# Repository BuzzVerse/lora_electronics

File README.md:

pliki do płytki beaglebone'a i esp32c3

Beaglebone + lora + bme280 najnowsza wersja:
https://github.com/BuzzVerse/lora_hardware/tree/main/beaglebone_gateway/v1

esp32c3 + lora + bme280 najnowsza wersja:
https://github.com/BuzzVerse/lora_hardware/tree/main/esp32_node/v1

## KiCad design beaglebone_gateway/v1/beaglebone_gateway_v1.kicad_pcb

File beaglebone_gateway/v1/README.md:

# LoRa gateway v1

This repository contains schematics and PCB for LoRa gateway HAT.

Screenshots can be found in `pdf` directory

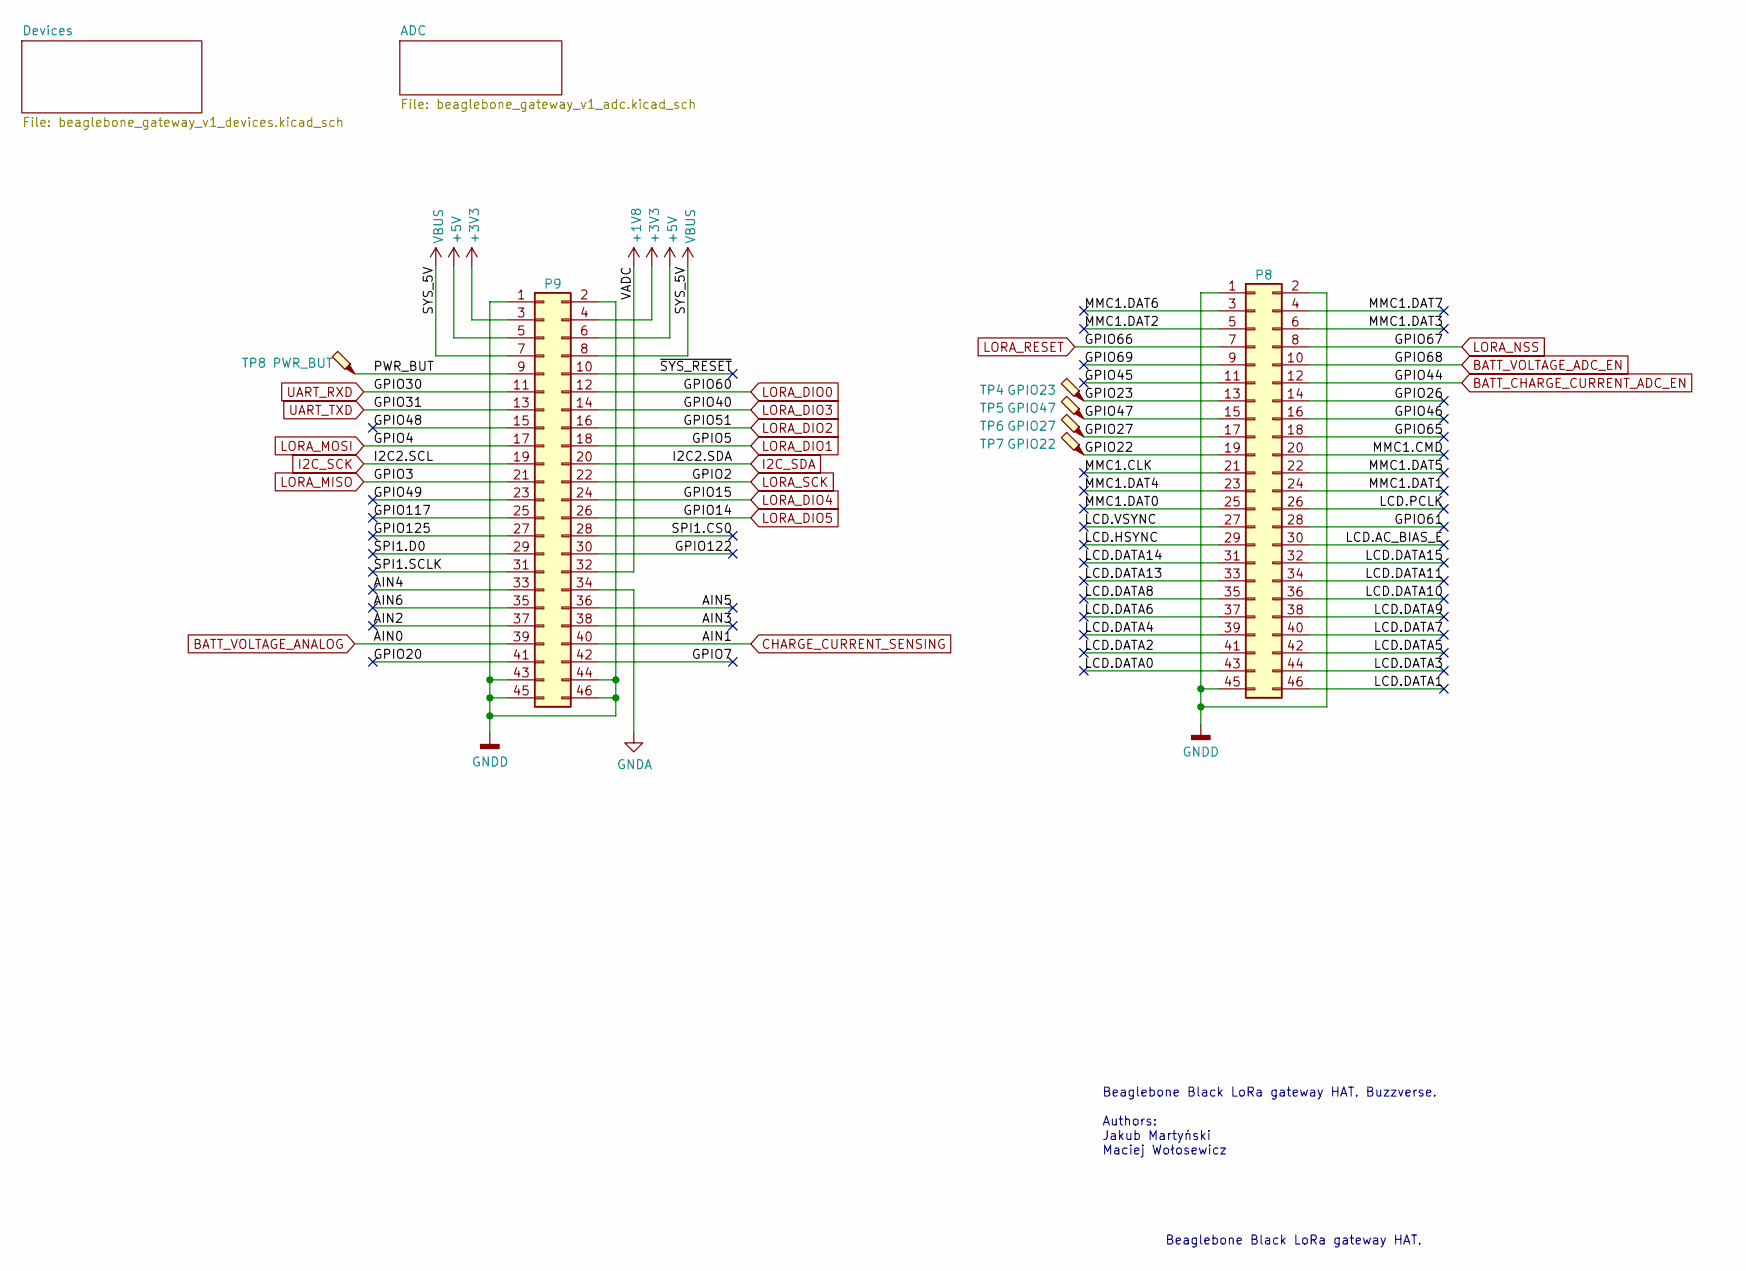
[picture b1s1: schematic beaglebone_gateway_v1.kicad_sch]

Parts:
P8, P9: BeagleBone_Black_Header; PinHeader_2x23_P2.54mm_Vertical
TP4: GPIO23; TestPoint_Pad_D1.5mm
TP5: GPIO47; TestPoint_Pad_D1.5mm
TP6: GPIO27; TestPoint_Pad_D1.5mm
TP7: GPIO22; TestPoint_Pad_D1.5mm
TP8: PWR_BUT; TestPoint_Pad_D1.5mm

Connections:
+1V8: P9.32
+3V3: P9.3, P9.4; also elsewhere on the board
+5V: P9.5, P9.6; also elsewhere on the board
/AIN2: P9.37
/AIN3: P9.38
/AIN4: P9.33
/AIN5: P9.36
/AIN6: P9.35
/GPIO7: P9.42
/GPIO20: P9.41
/GPIO22: P8.19, TP7.1
/GPIO23: P8.13, TP4.1
/GPIO26: P8.14
/GPIO27: P8.17, TP6.1
/GPIO45: P8.11
/GPIO46: P8.16
/GPIO47: P8.15, TP5.1
/GPIO48: P9.15
/GPIO49: P9.23
/GPIO61: P8.28
/GPIO65: P8.18
/GPIO69: P8.9
/GPIO117: P9.25
/GPIO122: P9.30
/GPIO125: P9.27
/LCD.AC_BIAS_E: P8.30
/LCD.DATA0: P8.43
/LCD.DATA1: P8.46
/LCD.DATA2: P8.41
/LCD.DATA3: P8.44
/LCD.DATA4: P8.39
/LCD.DATA5: P8.42
/LCD.DATA6: P8.37
/LCD.DATA7: P8.40
/LCD.DATA8: P8.35
/LCD.DATA9: P8.38
/LCD.DATA10: P8.36
/LCD.DATA11: P8.34
/LCD.DATA13: P8.33
/LCD.DATA14: P8.31
/LCD.DATA15: P8.32
/LCD.HSYNC: P8.29
/LCD.PCLK: P8.26
/LCD.VSYNC: P8.27
/MMC1.CLK: P8.21
/MMC1.CMD: P8.20
/MMC1.DAT0: P8.25
/MMC1.DAT1: P8.24
/MMC1.DAT2: P8.5
/MMC1.DAT3: P8.6
/MMC1.DAT4: P8.23
/MMC1.DAT5: P8.22
/MMC1.DAT6: P8.3
/MMC1.DAT7: P8.4
/PWR_BUT: P9.9, TP8.1
/SPI1.CS0: P9.28
/SPI1.D0: P9.29
/SPI1.SCLK: P9.31
/~SYS_RESET: P9.10
BATT_CHARGE_CURRENT_ADC_EN: P8.12; also elsewhere on the board
BATT_VOLTAGE_ADC_EN: P8.10; also elsewhere on the board
BATT_VOLTAGE_ANALOG: P9.39; also elsewhere on the board
CHARGE_CURRENT_SENSING: P9.40; also elsewhere on the board
GNDA: P9.34; also elsewhere on the board
GNDD: P8.1, P8.2, P8.45, P9.1, P9.2, P9.43, P9.44, P9.45, P9.46; also elsewhere on the board
I2C_SCK: P9.19; also elsewhere on the board
I2C_SDA: P9.20; also elsewhere on the board
LORA_DIO0: P9.12; also elsewhere on the board
LORA_DIO1: P9.18; also elsewhere on the board
LORA_DIO2: P9.16; also elsewhere on the board
LORA_DIO3: P9.14; also elsewhere on the board
LORA_DIO4: P9.24; also elsewhere on the board
LORA_DIO5: P9.26; also elsewhere on the board
LORA_MISO: P9.21; also elsewhere on the board
LORA_MOSI: P9.17; also elsewhere on the board
LORA_NSS: P8.8; also elsewhere on the board
LORA_RESET: P8.7; also elsewhere on the board
LORA_SCK: P9.22; also elsewhere on the board
UART_RXD: P9.11; also elsewhere on the board
UART_TXD: P9.13; also elsewhere on the board
VBUS: P9.7, P9.8

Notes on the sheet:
Beaglebone Black LoRa gateway HAT.
Beaglebone Black LoRa gateway HAT. Buzzverse. Authors: Jakub Martyński Maciej Wołosewicz

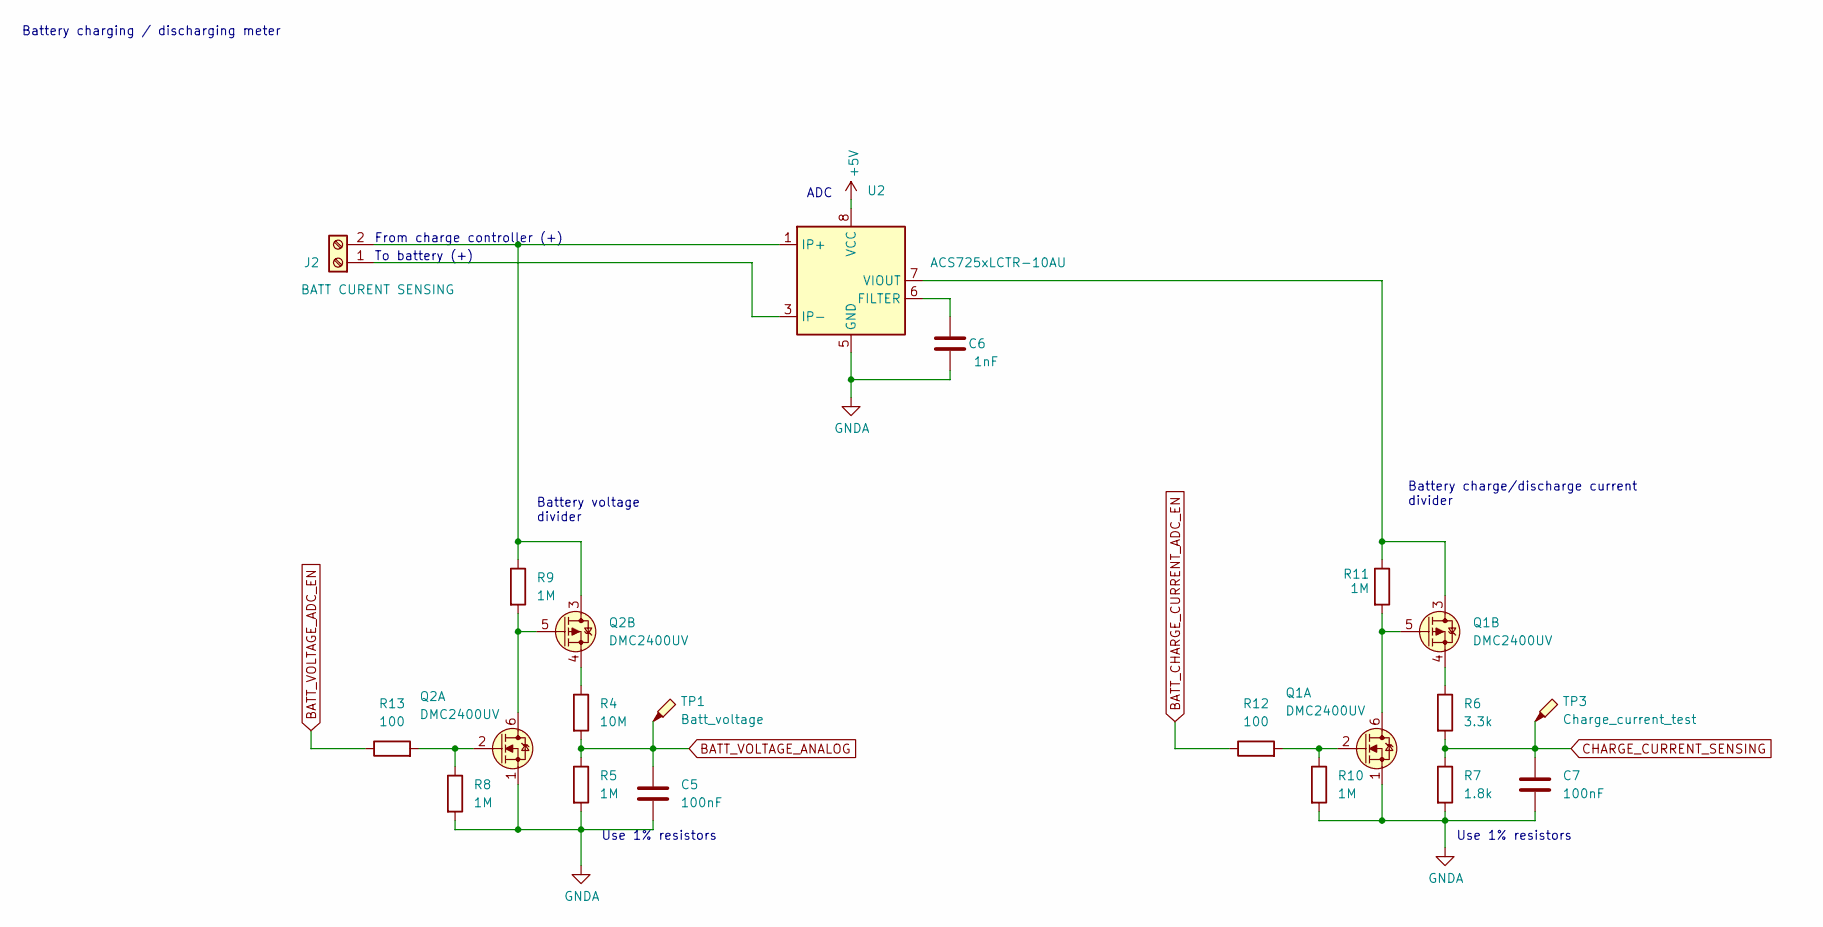
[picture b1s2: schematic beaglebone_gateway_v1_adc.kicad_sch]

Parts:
C5, C7: 100nF; C_0603_1608Metric
C6: 1nF; C_0603_1608Metric
J2: BATT CURENT SENSING; TerminalBlock_Phoenix_PT-1,5-2-3.5-H_1x02_P3.50mm_Horizontal
Q1, Q2: DMC2400UV; SOT-563
R4: 10M; R_0603_1608Metric
R5, R8, R9, R10, R11: 1M; R_0603_1608Metric
R6: 3.3k; R_0603_1608Metric
R7: 1.8k; R_0603_1608Metric
R12, R13: 100; R_0603_1608Metric
TP1: Batt_voltage; TestPoint_Pad_D1.5mm
TP3: Charge_current_test; TestPoint_Pad_D1.5mm
U2: ACS725xLCTR-10AU; SOIC-8_3.9x4.9mm_P1.27mm

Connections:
+5V: U2.8 (VCC); also elsewhere on the board
BATT_CHARGE_CURRENT_ADC_EN: R12.1; also elsewhere on the board
BATT_VOLTAGE_ADC_EN: R13.1; also elsewhere on the board
BATT_VOLTAGE_ANALOG: C5.1, R4.2, R5.1, TP1.1; also elsewhere on the board
CHARGE_CURRENT_SENSING: C7.1, R6.2, R7.1, TP3.1; also elsewhere on the board
GNDA: C5.2, C6.2, C7.2, Q1.1 (S1), Q2.1 (S1), R5.2, R7.2, R8.2, R10.2, U2.5 (GND); also elsewhere on the board
unnamed: J2.1, U2.3 (IP-), U2.4 (IP-)
unnamed: J2.2, Q2.3 (D2), R9.1, U2.1 (IP+), U2.2 (IP+)
unnamed: Q1.5 (G2), Q1.6 (D1), R11.2
unnamed: Q1.2 (G1), R10.1, R12.2
unnamed: Q1.3 (D2), R11.1, U2.7 (VIOUT)
unnamed: Q1.4 (S2), R6.1
unnamed: Q2.5 (G2), Q2.6 (D1), R9.2
unnamed: Q2.2 (G1), R8.1, R13.2
unnamed: Q2.4 (S2), R4.1
unnamed: C6.1, U2.6 (FILTER)

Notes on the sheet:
Battery charge/discharge current divider
ADC
Battery voltage divider
Battery charging / discharging meter
From charge controller (+)
Use 1% resistors
To battery (+)

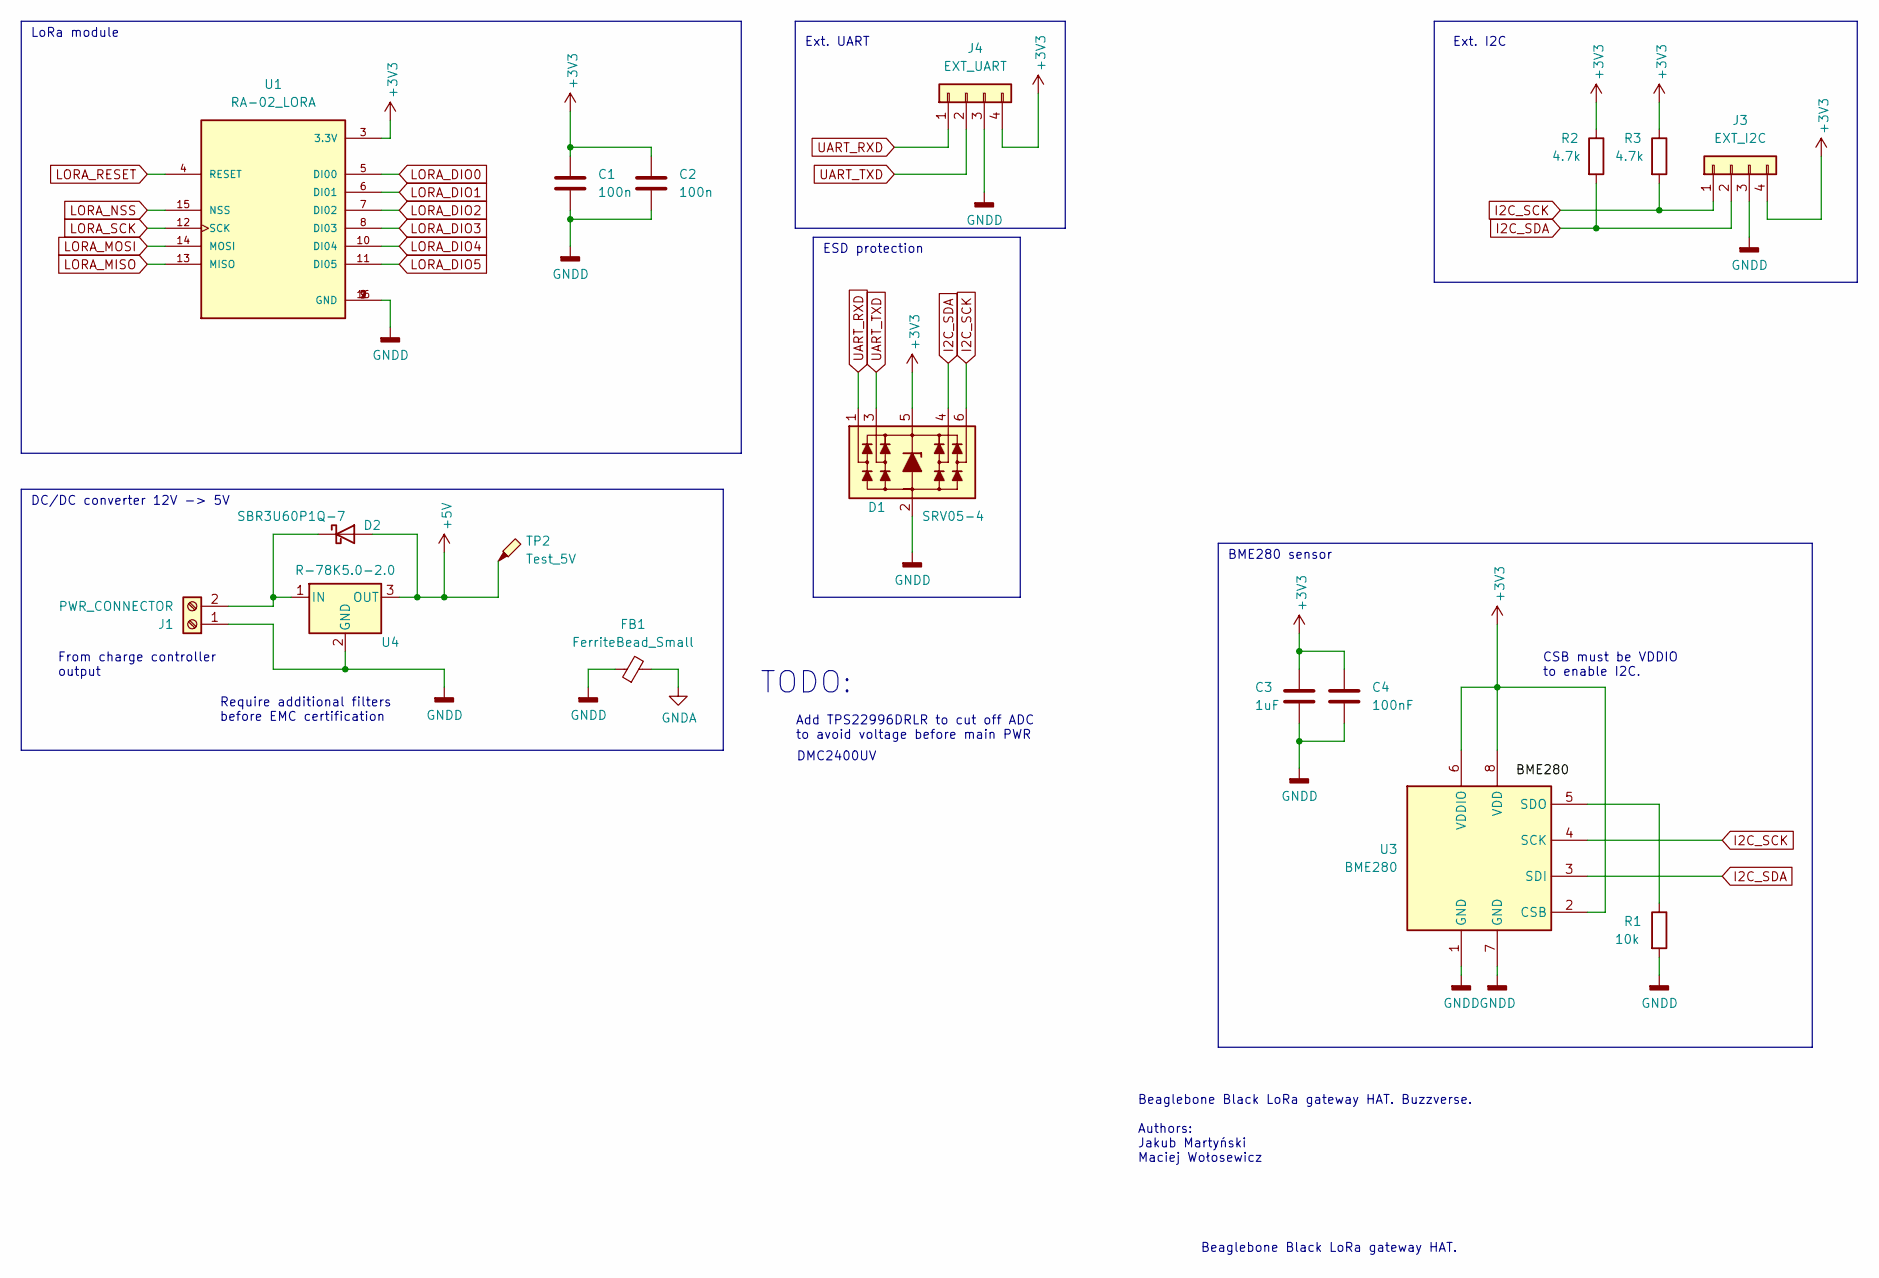
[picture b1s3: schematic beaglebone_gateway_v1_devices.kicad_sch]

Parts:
C1, C2: 100n; C_0603_1608Metric
C3: 1uF; C_0603_1608Metric
C4: 100nF; C_0603_1608Metric
D1: SRV05-4; SOT-23-6
D2: SBR3U60P1Q-7; D_PowerDI-123
FB1: FerriteBead_Small; Ferrite_0603_1608Metric
J1: PWR_CONNECTOR; TerminalBlock_Phoenix_PT-1,5-2-3.5-H_1x02_P3.50mm_Horizontal
J3: EXT_I2C; PinHeader_1x04_P2.54mm_Vertical
J4: EXT_UART; PinHeader_1x04_P2.54mm_Vertical
R1: 10k; R_0603_1608Metric
R2, R3: 4.7k; R_0603_1608Metric
TP2: Test_5V; TestPoint_Pad_D1.5mm
U1: RA-02_LORA; MODULE_RA-02_LORA; PARTREV 2018/03/02
U3: BME280; Bosch_LGA-8_2.5x2.5mm_P0.65mm_ClockwisePinNumbering
U4: R-78K5.0-2.0; Converter_DCDC_RECOM_R-78HB-0.5L_THT

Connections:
+3V3: C1.1, C2.1, C3.1, C4.1, D1.5 (VP), J3.4, J4.4, R2.1, R3.1, U1.3 (3.3V), U3.2 (CSB), U3.6 (VDDIO), U3.8 (VDD); also elsewhere on the board
+5V: D2.2 (A), TP2.1, U4.3 (OUT); also elsewhere on the board
GNDA: FB1.2; also elsewhere on the board
GNDD: C1.2, C2.2, C3.2, C4.2, D1.2 (VN), FB1.1, J1.1, J3.3, J4.3, R1.2, U1.1 (GND), U1.2 (GND), U1.9 (GND), U1.16 (GND), U3.1 (GND), U3.7 (GND), U4.2 (GND); also elsewhere on the board
I2C_SCK: D1.6 (L4), J3.1, R3.2, U3.4 (SCK); also elsewhere on the board
I2C_SDA: D1.4 (L3), J3.2, R2.2, U3.3 (SDI); also elsewhere on the board
LORA_DIO0: U1.5 (DI00); also elsewhere on the board
LORA_DIO1: U1.6 (DI01); also elsewhere on the board
LORA_DIO2: U1.7 (DI02); also elsewhere on the board
LORA_DIO3: U1.8 (DI03); also elsewhere on the board
LORA_DIO4: U1.10 (DI04); also elsewhere on the board
LORA_DIO5: U1.11 (DI05); also elsewhere on the board
LORA_MISO: U1.13 (MISO); also elsewhere on the board
LORA_MOSI: U1.14 (MOSI); also elsewhere on the board
LORA_NSS: U1.15 (NSS); also elsewhere on the board
LORA_RESET: U1.4 (RESET); also elsewhere on the board
LORA_SCK: U1.12 (SCK); also elsewhere on the board
unnamed: D2.1 (K), J1.2, U4.1 (IN)
unnamed: R1.1, U3.5 (SDO)
UART_RXD: D1.1 (L1), J4.1; also elsewhere on the board
UART_TXD: D1.3 (L2), J4.2; also elsewhere on the board

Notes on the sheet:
BME280 sensor
Require additional filters before EMC certification
Ext. I2C
TODO:
Ext. UART
Add TPS22996DRLR to cut off ADC to avoid voltage before main PWR
ESD protection
DMC2400UV
Beaglebone Black LoRa gateway HAT. Buzzverse. Authors: Jakub Martyński Maciej Wołosewicz
DC/DC converter 12V -> 5V
LoRa module
Beaglebone Black LoRa gateway HAT.
CSB must be VDDIO to enable I2C.
From charge controller output

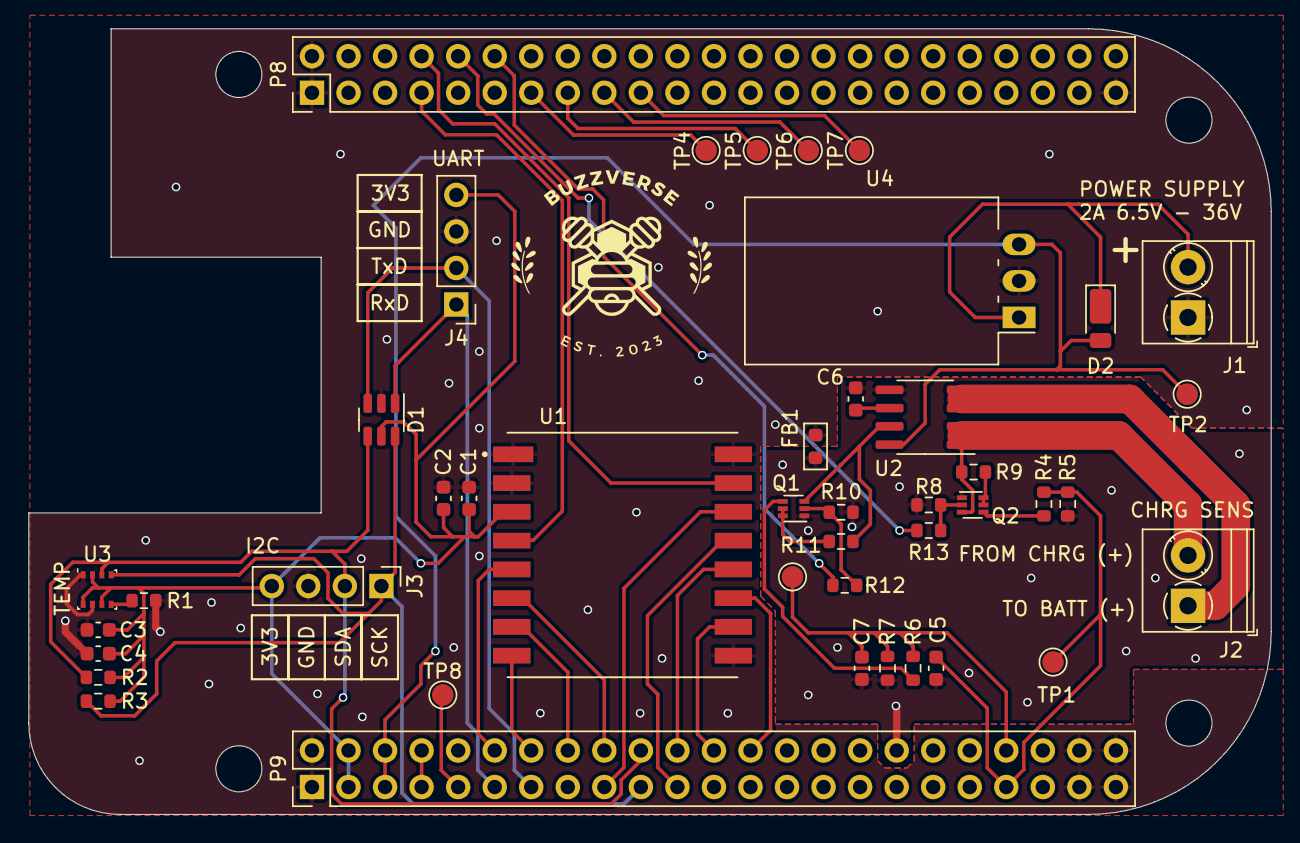
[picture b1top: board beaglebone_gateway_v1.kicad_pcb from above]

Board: 2 copper layers, 86.4 x 54.6 mm, 47 parts (0 on the bottom side), 41 nets.

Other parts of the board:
MH1, MH2, MH3, MH4: MountingHole_3.2mm_M3_DIN965

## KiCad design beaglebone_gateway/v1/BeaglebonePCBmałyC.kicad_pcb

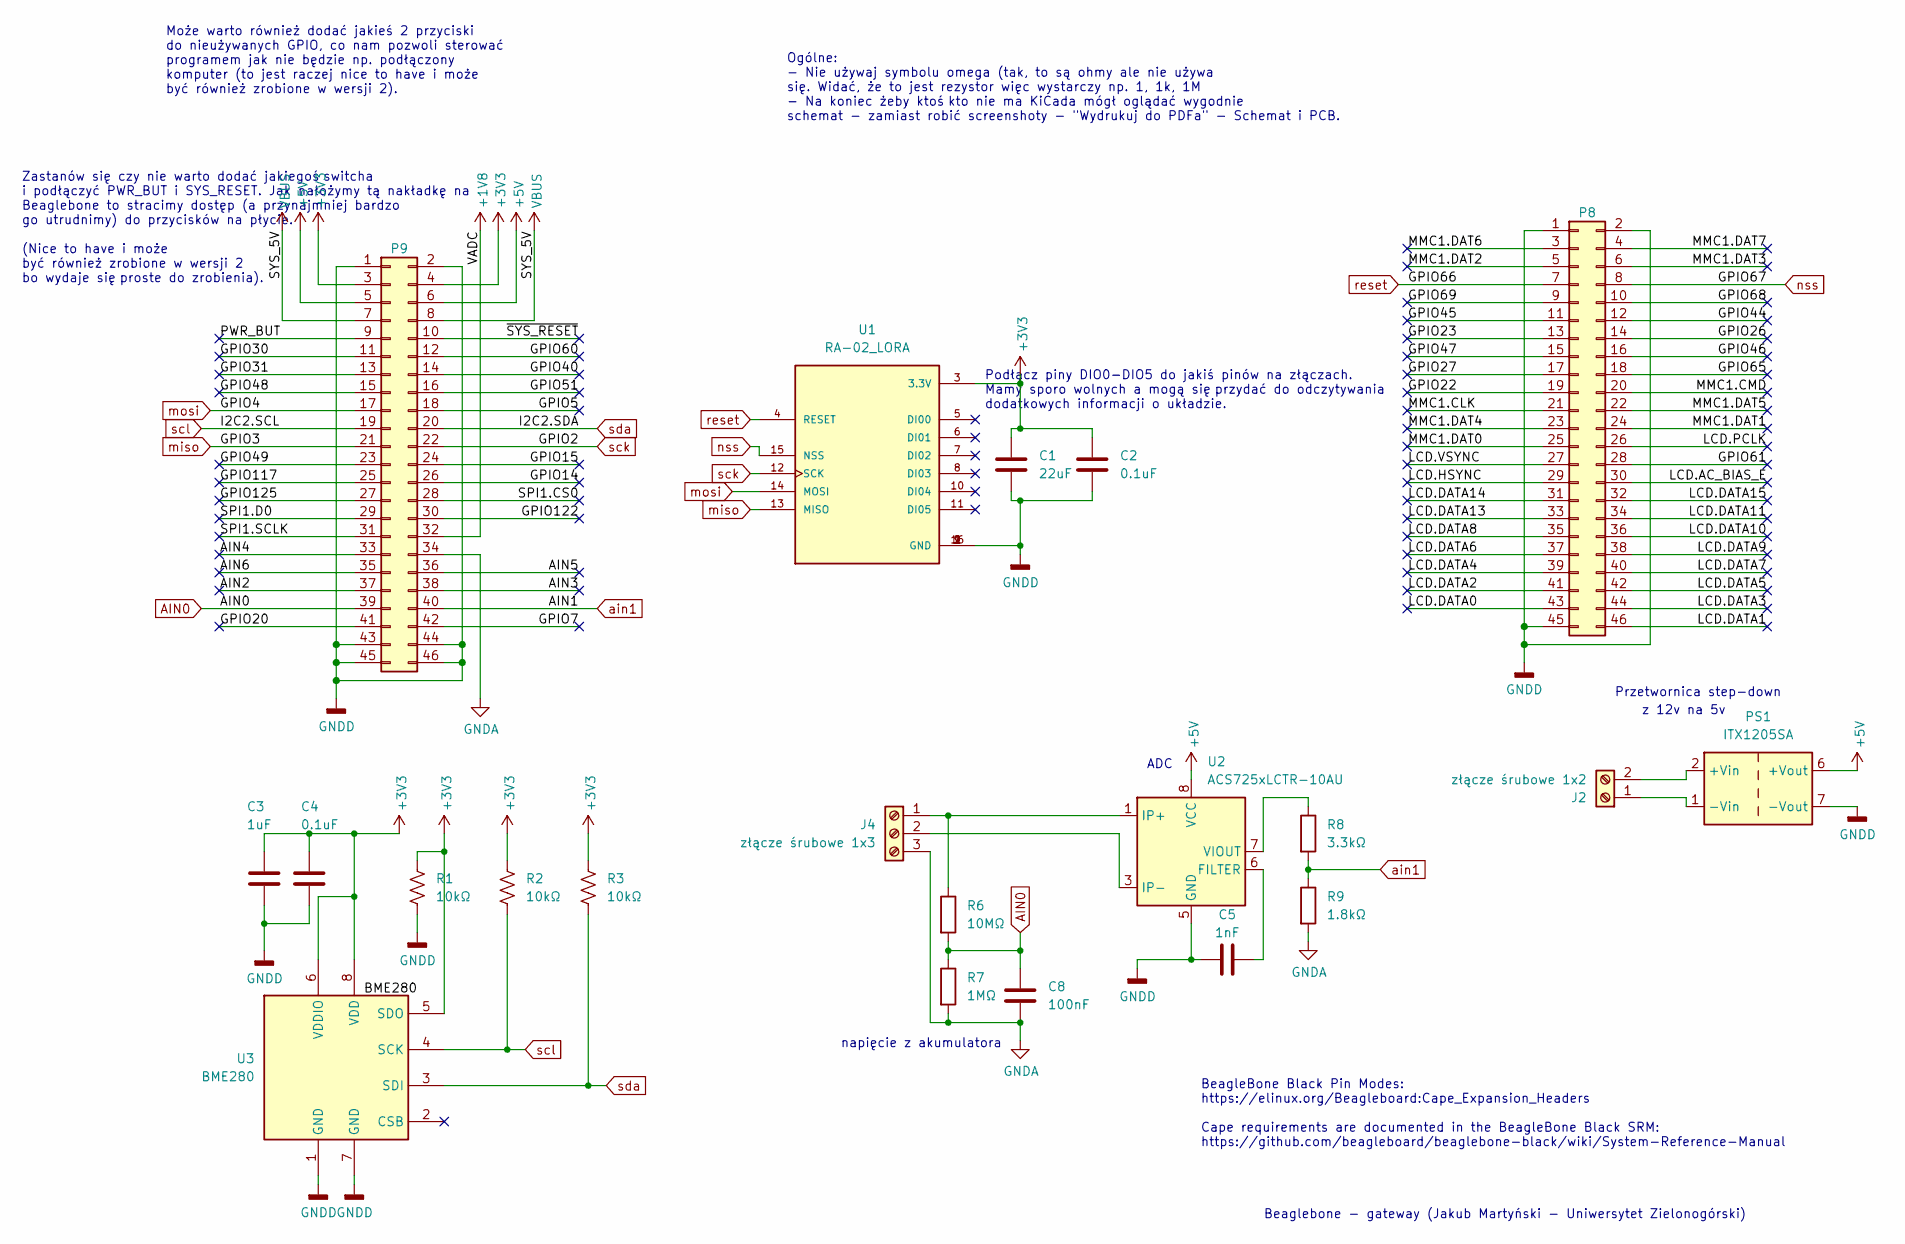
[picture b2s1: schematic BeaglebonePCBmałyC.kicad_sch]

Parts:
C1: 22uF; C_0603_1608Metric
C2, C4: 0.1uF; C_0603_1608Metric
C3: 1uF; C_0603_1608Metric
C5: 1nF; C_0603_1608Metric
C8: 100nF; C_0603_1608Metric
J2: złącze śrubowe 1x2; TerminalBlock_Phoenix_PT-1,5-2-3.5-H_1x02_P3.50mm_Horizontal
J4: złącze śrubowe 1x3; TerminalBlock_Phoenix_PT-1,5-3-3.5-H_1x03_P3.50mm_Horizontal
P8, P9: BeagleBone_Black_Header; PinHeader_2x23_P2.54mm_Vertical
PS1: ITX1205SA; Converter_DCDC_XP_POWER-ITXxxxxSA_THT
R1, R2, R3: 10kΩ; R_0603_1608Metric
R6: 10MΩ; R_0603_1608Metric
R7: 1MΩ; R_0603_1608Metric
R8: 3.3kΩ; R_0603_1608Metric
R9: 1.8kΩ; R_0603_1608Metric
U1: RA-02_LORA; MODULE_RA-02_LORA; PARTREV 2018/03/02
U2: ACS725xLCTR-10AU; SOIC-8_3.9x4.9mm_P1.27mm
U3: BME280; Bosch_LGA-8_2.5x2.5mm_P0.65mm_ClockwisePinNumbering

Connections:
+1V8: P9.32
+3V3: C1.1, C2.1, C3.1, C4.1, P9.3, P9.4, R1.1, R2.1, R3.1, U1.3 (3.3V), U3.5 (SDO), U3.6 (VDDIO), U3.8 (VDD)
+5V: P9.5, P9.6, PS1.6 (+Vout), U2.8 (VCC)
/AIN2: P9.37
/AIN3: P9.38
/AIN4: P9.33
/AIN5: P9.36
/AIN6: P9.35
/GPIO5: P9.18
/GPIO7: P9.42
/GPIO14: P9.26
/GPIO15: P9.24
/GPIO20: P9.41
/GPIO22: P8.19
/GPIO23: P8.13
/GPIO26: P8.14
/GPIO27: P8.17
/GPIO30: P9.11
/GPIO31: P9.13
/GPIO40: P9.14
/GPIO44: P8.12
/GPIO45: P8.11
/GPIO46: P8.16
/GPIO47: P8.15
/GPIO48: P9.15
/GPIO49: P9.23
/GPIO51: P9.16
/GPIO60: P9.12
/GPIO61: P8.28
/GPIO65: P8.18
/GPIO68: P8.10
/GPIO69: P8.9
/GPIO117: P9.25
/GPIO122: P9.30
/GPIO125: P9.27
/LCD.AC_BIAS_E: P8.30
/LCD.DATA0: P8.43
/LCD.DATA1: P8.46
/LCD.DATA2: P8.41
/LCD.DATA3: P8.44
/LCD.DATA4: P8.39
/LCD.DATA5: P8.42
/LCD.DATA6: P8.37
/LCD.DATA7: P8.40
/LCD.DATA8: P8.35
/LCD.DATA9: P8.38
/LCD.DATA10: P8.36
/LCD.DATA11: P8.34
/LCD.DATA13: P8.33
/LCD.DATA14: P8.31
/LCD.DATA15: P8.32
/LCD.HSYNC: P8.29
/LCD.PCLK: P8.26
/LCD.VSYNC: P8.27
/MMC1.CLK: P8.21
/MMC1.CMD: P8.20
/MMC1.DAT0: P8.25
/MMC1.DAT1: P8.24
/MMC1.DAT2: P8.5
/MMC1.DAT3: P8.6
/MMC1.DAT4: P8.23
/MMC1.DAT5: P8.22
/MMC1.DAT6: P8.3
/MMC1.DAT7: P8.4
/PWR_BUT: P9.9
/SPI1.CS0: P9.28
/SPI1.D0: P9.29
/SPI1.SCLK: P9.31
/~SYS_RESET: P9.10
AIN0: C8.1, P9.39, R6.2, R7.1
GNDA: C8.2, J4.3, P9.34, R7.2, R9.2
GNDD: C1.2, C2.2, C3.2, C4.2, C5.2, P8.1, P8.2, P8.45, P9.1, P9.2, P9.43, P9.44, P9.45, P9.46, PS1.7 (-Vout), R1.2, U1.1 (GND), U1.2 (GND), U1.9 (GND), U1.16 (GND), U2.5 (GND), U3.1 (GND), U3.7 (GND)
unnamed: J2.1, PS1.1 (-Vin)
unnamed: J2.2, PS1.2 (+Vin)
unnamed: J4.1, R6.1, U2.1 (IP+), U2.2 (IP+)
unnamed: J4.2, U2.3 (IP-), U2.4 (IP-)
unnamed: C5.1, U2.6 (FILTER)
unnamed: R8.1, U2.7 (VIOUT)
VBUS: P9.7, P9.8
ain1: P9.40, R8.2, R9.1
miso: P9.21, U1.13 (MISO)
mosi: P9.17, U1.14 (MOSI)
nss: P8.8, U1.15 (NSS)
reset: P8.7, U1.4 (RESET)
sck: P9.22, U1.12 (SCK)
scl: P9.19, R2.2, U3.4 (SCK)
sda: P9.20, R3.2, U3.3 (SDI)

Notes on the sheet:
Beaglebone - gateway (Jakub Martyński - Uniwersytet Zielonogórski)
BeagleBone Black Pin Modes: https://elinux.org/Beagleboard:Cape_Expansion_Headers Cape requirements are documented in the BeagleBone Black SRM: https://github.com/beagleboard/beaglebone-black/wiki/System-Reference-Manual
Podłącz piny DIO0-DIO5 do jakiś pinów na złączach. Mamy sporo wolnych a mogą się przydać do odczytywania dodatkowych informacji o układzie.
Może warto również dodać jakieś 2 przyciski do nieużywanych GPIO, co nam pozwoli sterować programem jak nie będzie np. podłączony komputer (to jest raczej nice to have i może być również zrobione w wersji 2).
Przetwornica step-down
napięcie z akumulatora
ADC
Ogólne: - Nie używaj symbolu omega (tak, to są ohmy ale nie używa się. Widać, że to jest rezystor więc wystarczy np. 1, 1k, 1M - Na koniec żeby ktoś kto nie ma KiCada mógł oglądać wygodnie schemat - zamiast robić screenshoty - "Wydrukuj do PDFa" - Schemat i PCB.
Zastanów się czy nie warto dodać jakiegoś switcha i podłączyć PWR_BUT i SYS_RESET. Jak nałożymy tą nakładkę na Beaglebone to stracimy dostęp (a przynajmniej bardzo go utrudnimy) do przycisków na płycie. (Nice to have i może być również zrobione w wersji 2 bo wydaje się proste do zrobienia).
z 12v na 5v

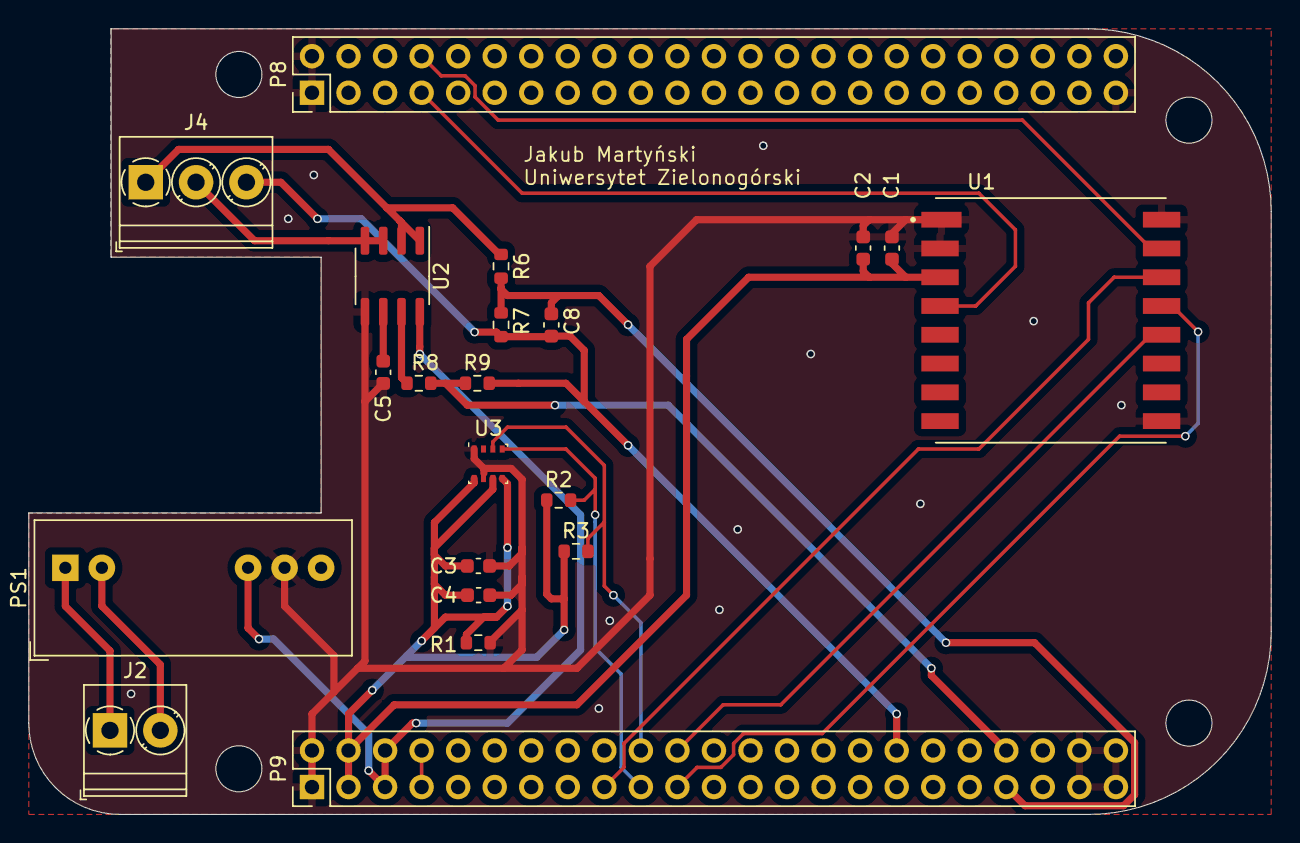
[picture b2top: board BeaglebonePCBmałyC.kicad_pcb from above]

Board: 2 copper layers, 86.4 x 54.6 mm, 25 parts (0 on the bottom side), 20 nets.

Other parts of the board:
MH1, MH2, MH3, MH4: MountingHole_3.2mm_M3_DIN965

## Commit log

2023-12-18 Schemat do esp32-c3 + bme + lora
    schemat na brudno w paincie
2023-12-18 schemat do beaglebone + lora
    Schemat na brudno w paincie
2024-01-30 Delete Beaglebone+bme280_KiCad7 directory
    Wrzucam ponownie bardziej poukładane
2024-01-30 Delete Beaglebone_KiCad7 directory
    wrzucam ponownie bardziej poukładane
2024-01-30 Delete Beaglebone+bme280_KiCad7v2 directory
    wrzucam ponownie bardziej poukładane
2024-03-14 pliki potrzebne do wydrukowania płytki
2024-04-04 poprawki
2024-04-04 Rename Gotowa_plytka.zip to Gotowa_Plytka.zip
2024-04-04 Review and some repo cleaning.
2024-04-04 Add .gitignore file
2024-04-15 update mały nawet nie warto mówić co zmieniłem
2024-05-10 Redesign of the board, reorganize and rename files
2024-05-10 Remove comments, add sheets description
2024-05-10 Add board images as pdfs
2024-05-10 Remove images from README. Add simple description stub
2024-05-14 Add ADC divider cut off using complementary mosfet transistors
2024-06-10 Add second version of LoRa PCB.
2024-06-10 Add images for LoRa node v2
